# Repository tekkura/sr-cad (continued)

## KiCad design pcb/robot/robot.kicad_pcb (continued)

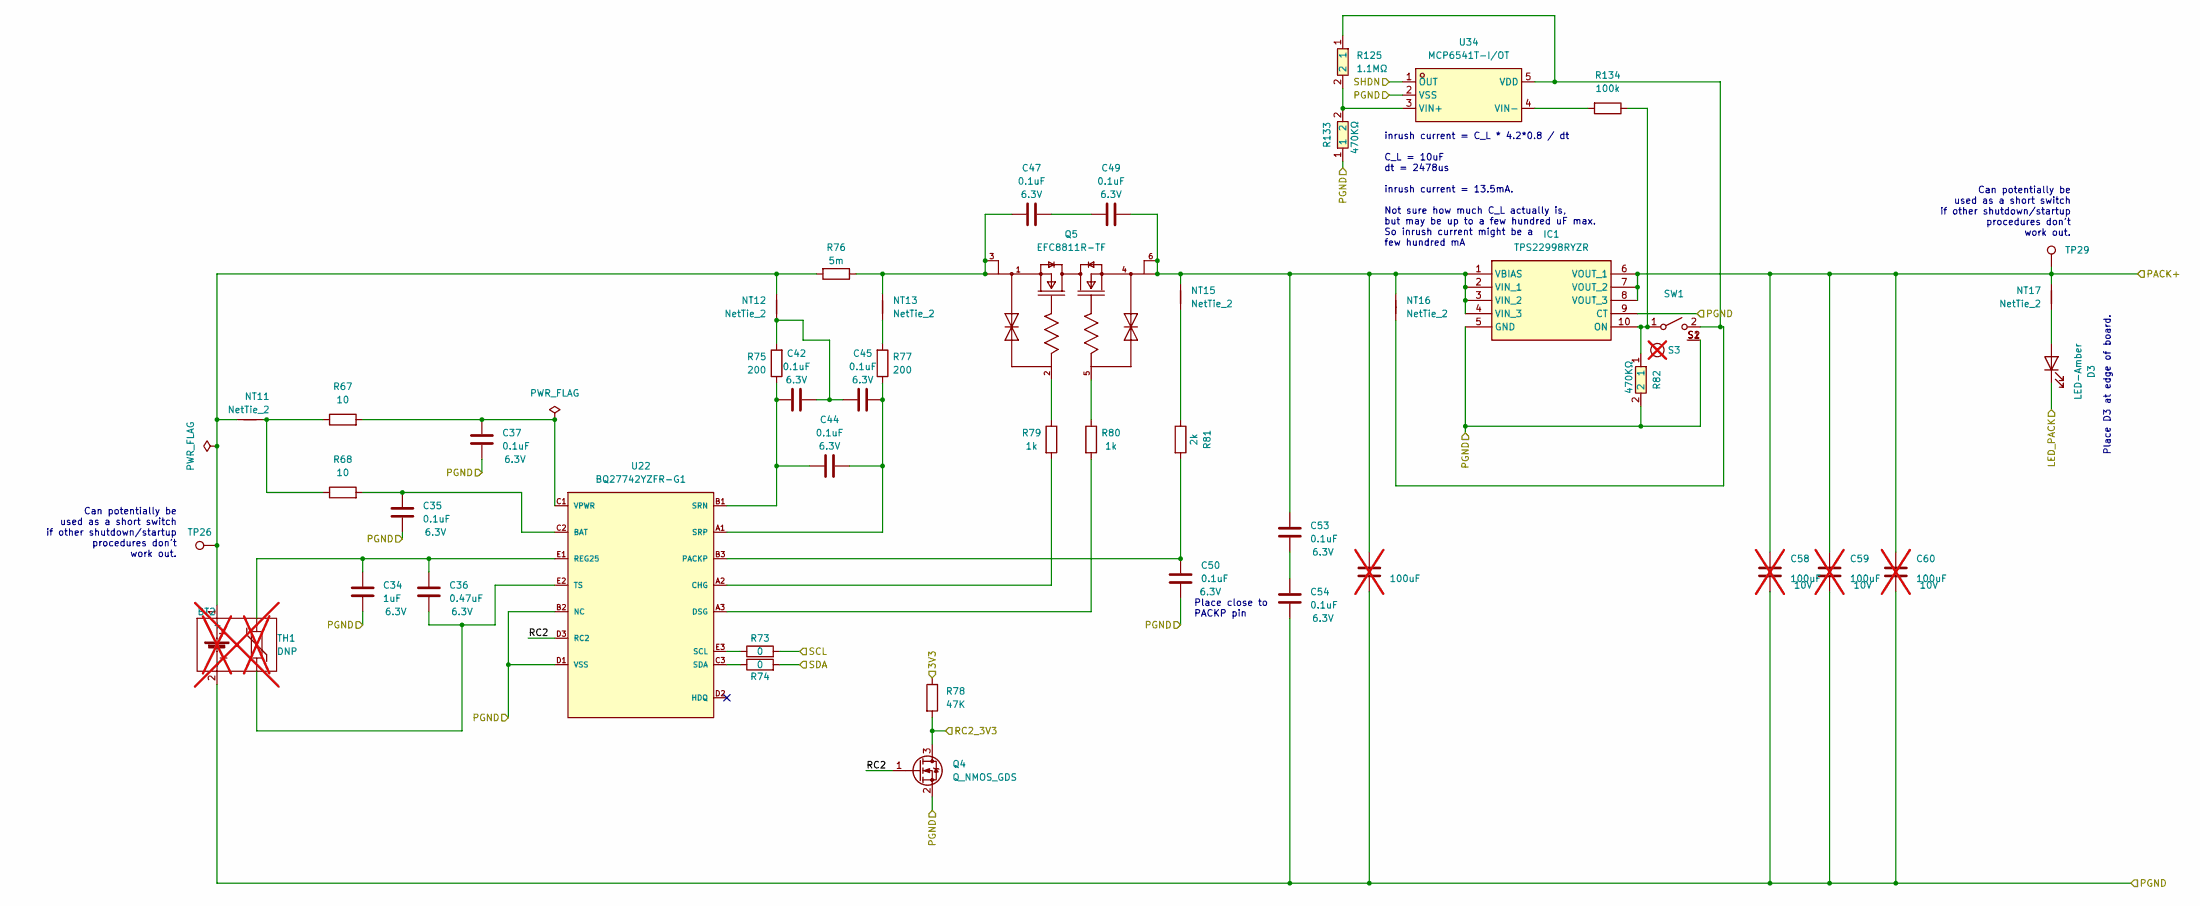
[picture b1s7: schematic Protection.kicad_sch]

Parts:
BT1: DNP; battery26650; Part Number 26650-5000-1; not fitted
BT2: DNP; battery26650_holderOnly; Part Number a15042300ux0145; not fitted
C34: 1uF; C_0402_1005Metric; Part Number GRM155R61E105KA12D
C35, C37, C42, C44, C45, C47, C49, C50, C53, C54: 0.1uF; C_0402_1005Metric; Part Number CL05A104KA5NNNC
C36: 0.47uF; C_0603_1608Metric; Part Number CL10B474KO8NNNC
C56, C58, C59, C60: 100uF; C_1206_3216Metric; Part Number GRM31CD80J107MEA8K; not fitted
D3: LED-Amber; B12H1UYG-20D000134U1930; Part Number B12H1UY--20D000134U1930
IC1: TPS22998RYZR; Part Number TPS22998RYZR
NT11, NT12, NT13, NT15, NT16, NT17: NetTie_2; NetTie-_SMD_Pad6mil; Part Number N/A
Q4: Q_NMOS_GDS; SOT-23; Part Number BSS138
Q5: EFC8811R-TF; ON_Semiconductor-568AL-10_2013-O-MFG; Part Number EFC8811R-TF
R67, R68: 10; R_0402_1005Metric; Part Number RC0402FR-1310RL
R73, R74: 0; R_0603_1608Metric; Part Number RMCF0603ZT0R00
R75, R77: 200; R_0603_1608Metric; Part Number ERJ-PA3J201V
R76: 5m; R_0805_2012Metric; Part Number PA0805FRF470R005L
R78: 47K; R_0603_1608Metric; Part Number RMCF0603JT47K0
R79, R80: 1k; R_0402_1005Metric; Part Number WR04X102 JTL
R81: 2k; R_0603_1608Metric; Part Number RMCF0603FT2K00
R82, R133: 0402WGJ0474TCE; R0402; MPN 0402WGJ0474TCE; LCSC Part C25562
R125: 1.1MΩ; R0402; Part Number 0402WGF1104TCE; LCSC Part C133039
R134: 100k; R_0402_1005Metric; Part Number 0402WGF1003TCE
S3: Part Number SW-R3-1A-A-1-2; not fitted
SW1: SW_SPST; MOLEX_picoblade_SMT_2pin; Part Number 0533980271
TH1: DNP; battery26650_thermistor; Part Number 103AT-5-1P-FT; not fitted
TP26, TP29: TestPoint; THT_JumperLead; Part Number N/A
U22: BQ27742YZFR-G1; Texas_Instruments-YZF0015-0-0-MFG; Part Number BQ27742YZFR-G1
U34: MCP6541T-I/OT; SOT-23-5_L3.0-W1.7-P0.95-LS2.8-BR; Part Number MCP6541T-I/OT; LCSC Part C80839

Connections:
/3V3: R78.1; also elsewhere on the board
/GPIO20: Q4.3 (D), R78.2; also elsewhere on the board
/I2C0_SCL: R73.2; also elsewhere on the board
/I2C0_SDA: R74.2; also elsewhere on the board
/LED_PACK: D3.1 (K); also elsewhere on the board
/Protection/PACK+: C58.1, C59.1, C60.1, IC1.6 (VOUT_1), IC1.7 (VOUT_2), IC1.8 (VOUT_3), NT17.1, TP29.1; also elsewhere on the board
/Protection/RC2: Q4.1 (G), U22.D3 (RC2)
/SHDN: U34.1 (OUT); also elsewhere on the board
GND: BT2.2 (-), C34.2, C35.2, C37.2, C50.2, C54.2, C56.2, C58.2, C59.2, C60.2, IC1.5 (GND), IC1.9 (CT), Q4.2 (S), R82.2, R133.1, SW1.S1, SW1.S2, U22.B2 (NC), U22.D1 (VSS), U34.2 (VSS); also elsewhere on the board
unnamed: BT2.1 (+), NT11.2, NT12.1, R76.2, TP26.1
unnamed: C42.2, C45.1, NT12.2, R75.2
unnamed: C47.1, NT13.1, Q5.1 (SOURCE1), Q5.3 (SOURCE1), R76.1
unnamed: C47.2, C49.1
unnamed: C53.2, C54.1
unnamed: D3.2 (A), NT17.2
unnamed: IC1.10 (ON), R82.1, R134.1, SW1.1 (A)
unnamed: C49.2, C53.1, C56.1, IC1.1 (VBIAS), IC1.2 (VIN_1), IC1.3 (VIN_2), IC1.4 (VIN_3), NT15.1, NT16.1, Q5.4 (SOURCE2), Q5.6 (SOURCE2)
unnamed: NT11.1, R67.1, R68.1
unnamed: NT13.2, R77.2
unnamed: NT15.2, R81.1
unnamed: Q5.2 (GATE1), R79.1
unnamed: Q5.5 (GATE2), R80.1
unnamed: NT16.2, R125.1, SW1.2 (B), U34.5 (VDD)
unnamed: C35.1, R68.2, U22.C2 (BAT)
unnamed: R79.2, U22.A2 (CHG)
unnamed: R80.2, U22.A3 (DSG)
unnamed: C50.1, R81.2, U22.B3 (PACKP)
unnamed: C34.1, C36.1, TH1.1, U22.E1 (REG25)
unnamed: R73.1, U22.E3 (SCL)
unnamed: R74.1, U22.C3 (SDA)
unnamed: C42.1, C44.1, R75.1, U22.B1 (SRN)
unnamed: C44.2, C45.2, R77.1, U22.A1 (SRP)
unnamed: C36.2, TH1.2, U22.E2 (TS)
unnamed: C37.1, R67.2, U22.C1 (VPWR)
unnamed: R125.2, R133.2, U34.3 (VIN+)
unnamed: R134.2, U34.4 (VIN-)

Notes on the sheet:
Can potentially be used as a short switch if other shutdown/startup procedures don't work out.
inrush current = C_L * 4.2*0.8 / dt C_L = 10uF dt = 2478us inrush current = 13.5mA. Not sure how much C_L actually is, but may be up to a few hundred uF max. So inrush current might be a few hundred mA
Place D3 at edge of board.
Place close to PACKP pin

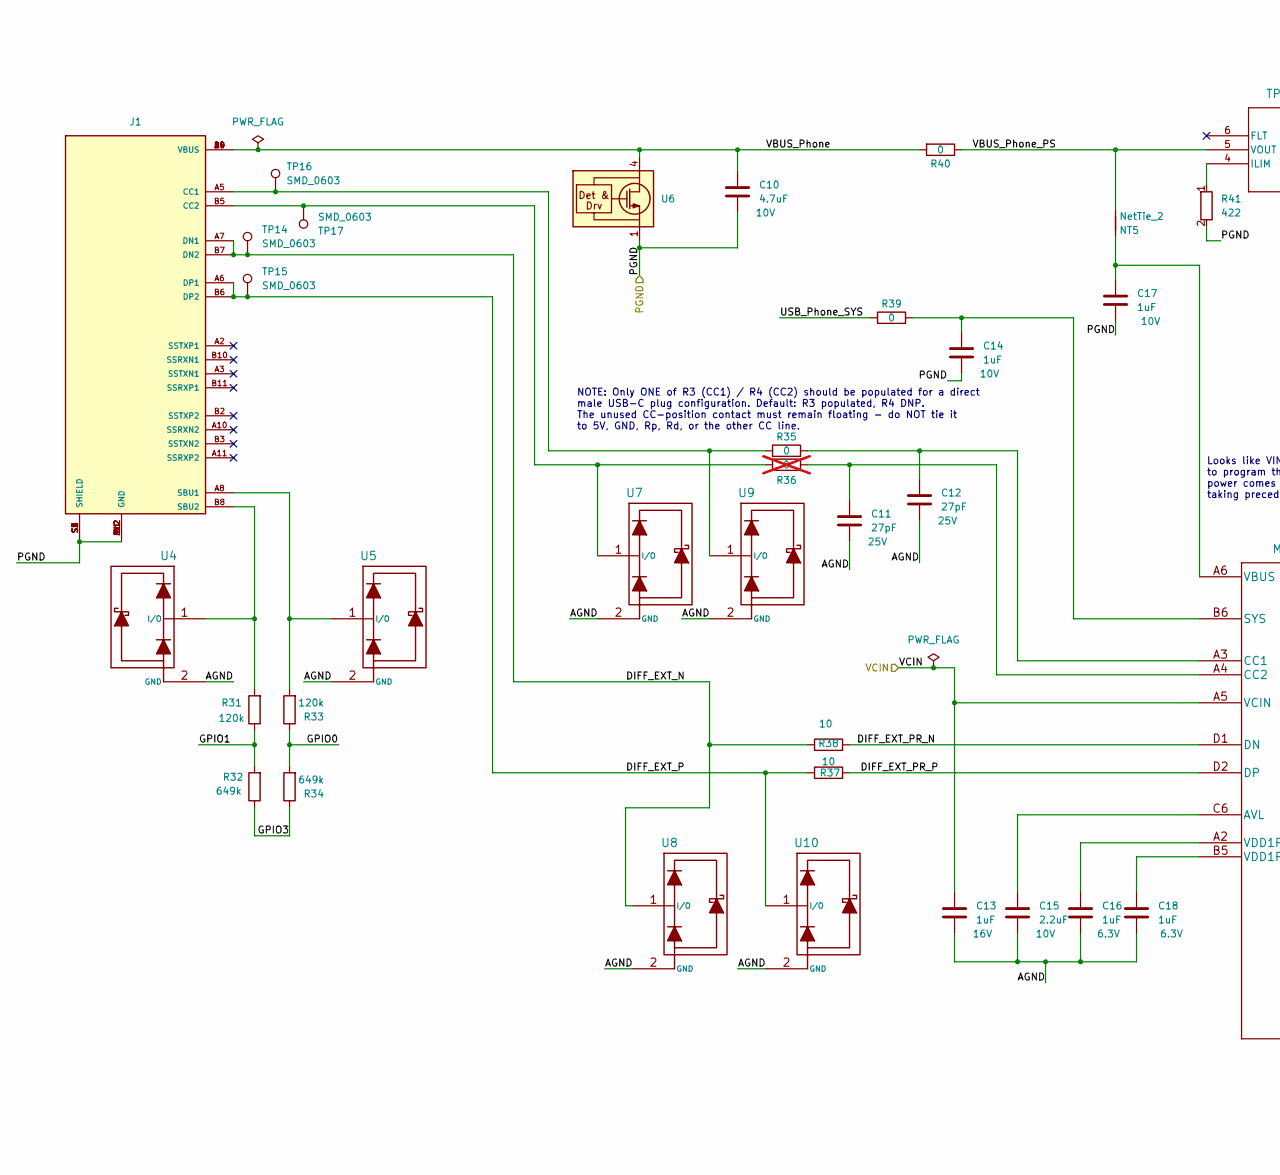
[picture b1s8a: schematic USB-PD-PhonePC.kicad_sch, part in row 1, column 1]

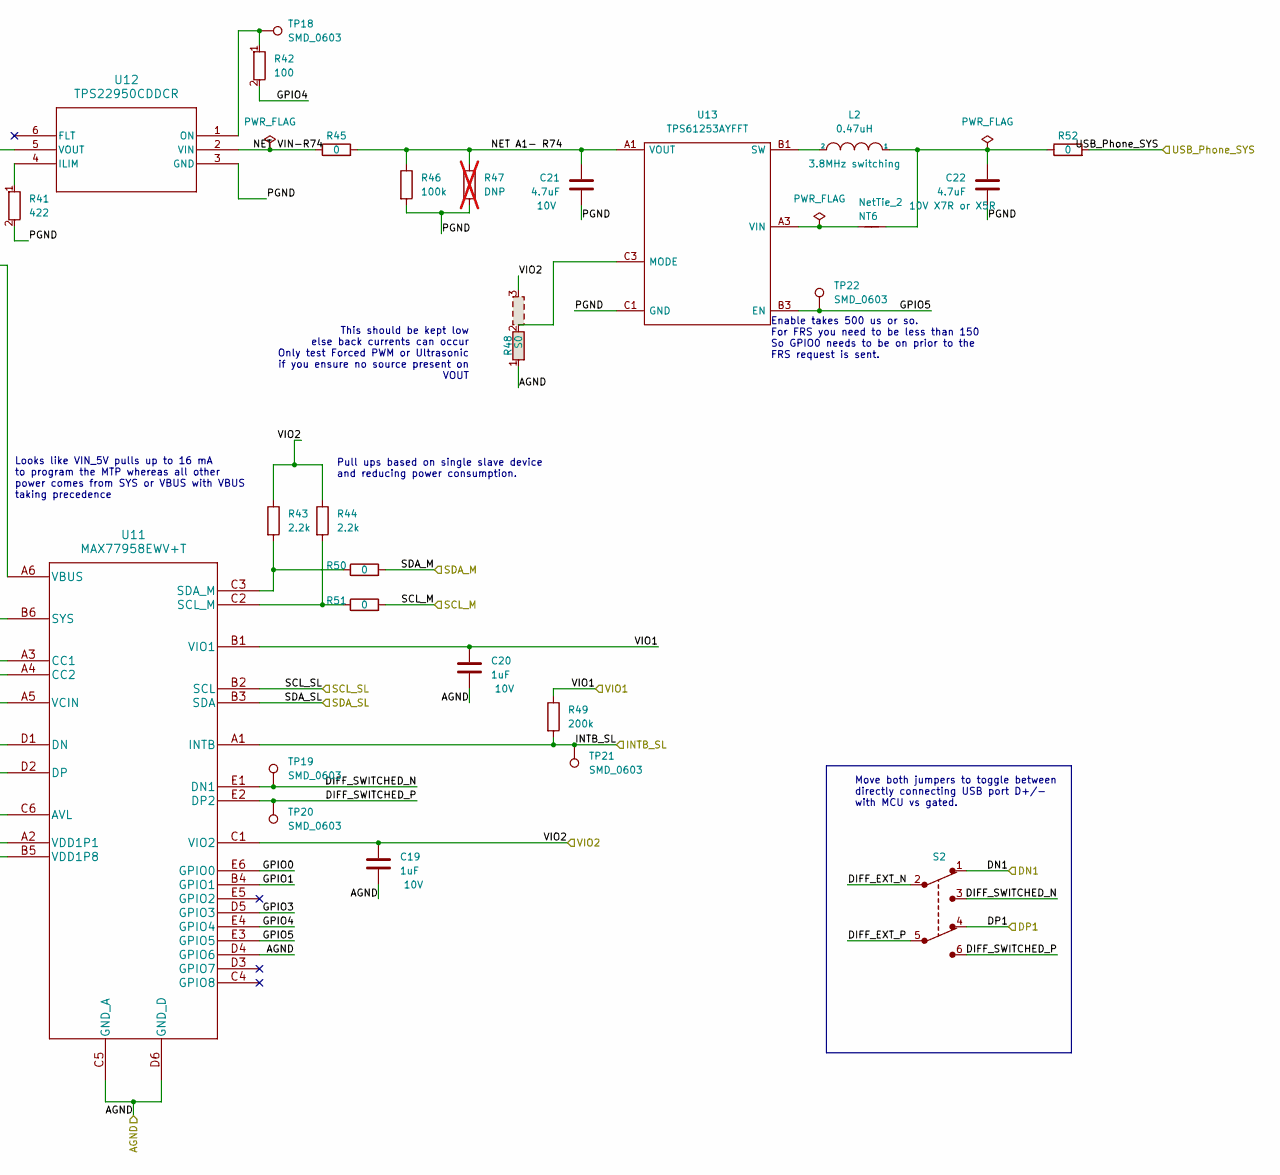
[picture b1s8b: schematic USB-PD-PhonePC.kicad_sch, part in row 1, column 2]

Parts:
C10, C21, C22: 4.7uF; C_0603_1608Metric; Part Number GRM188R61E475KE11D
C11, C12: 27pF; C_0402_1005Metric; Part Number GRM1555C1H270JA01J
C13, C14, C16, C17, C18, C19, C20: 1uF; C_0402_1005Metric; Part Number GRM155R61E105KA12D
C15: 2.2uF; C_0603_1608Metric; Part Number CL10A225KP8NNNC
J1: USB4151-GF-C; GCT_USB4151-GF-C_REVA; Part Number USB4151-GF-C
L2: 0.47uH; Vishay-IHLP-2020BZ-FP_1.905x2.79-3D_2.0-0-0-MFG; Part Number IHLP2020BZERR47M01
NT5, NT6: NetTie_2; NetTie-_SMD_Pad6mil; Part Number N/A
R31, R33: 120k; R_0603_1608Metric; Part Number RMCF0603JT120K
R32, R34: 649k; R_0603_1608Metric; Part Number ERJ-3EKF6493V
R35, R39, R50, R51, R52: 0; R_0603_1608Metric; Part Number RMCF0603ZT0R00
R36: 0; R_0603_1608Metric; Part Number RMCF0603ZT0R00; not fitted
R37, R38: 10; R_0402_1005Metric; Part Number RC0402FR-1310RL
R40, R45: 0; R_0805_2012Metric; Part Number RMCF0805ZT0R00
R41: 422; R_0402_1005Metric; Part Number RC0402FR-07422RL; DigiKey_Part_Number YAG3158CT-ND
R42: 100; R_0402_1005Metric; Part Number RC0402FR-07100RL; DigiKey_Part_Number 311-100LRCT-ND
R43, R44: 2.2k; R_0603_1608Metric; Part Number RMCF0603JT2K20
R46: 100k; R_0603_1608Metric; Part Number WR06X1003FTL
R47: DNP; R_0603_1608Metric; Part Number DNP; not fitted
R48: S0; R_0603_1608Metric_3pin_Switch; Part Number RMCF0603ZT0R00
R49: 200k; R_0603_1608Metric; Part Number RMCF0603JT200K
S2: JS202011JCQN; SW_JS202011JCQN; Part Number JS202011JCQN
TP14, TP15, TP16, TP17, TP18, TP19, TP20, TP21, TP22: SMD_0603; TestPoint_SMD_0603; Part Number RCUCTE
U4, U5, U7, U8, U9, U10: TPD1E05U06; TPD1E05U06DPYR; Part Number TPD1E05U06DPYR
U6: TVS0500DRV; TVS0500DRVR; Part Number TVS0500DRVR
U11: MAX77958EWV+T; MAX77958EWV&plus_T; Part Number MAX77958EWV+T
U12: TPS22950CDDCR; DDC6_TEX; Part Number TPS22950CDDCR
U13: TPS61253AYFFT; Texas_Instruments-YFF0009-BGA9C40P3X3_119X129X62; Part Number TPS61253AYFFT

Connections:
/DN1: S2.1; also elsewhere on the board
/DP1: S2.4; also elsewhere on the board
/GPIO7: R49.2, TP21.1, U11.A1 (INTB); also elsewhere on the board
/I2C1_SCL: R51.2; also elsewhere on the board
/I2C1_SDA: R50.2; also elsewhere on the board
/SCL_SL: U11.B2 (SCL); also elsewhere on the board
/SDA_SL: U11.B3 (SDA); also elsewhere on the board
/USB-PD-PhonePC/DIFF_EXT_N: J1.A7 (DN1), J1.B7 (DN2), R38.1, S2.2, TP14.1, U8.1 (I/O)
/USB-PD-PhonePC/DIFF_EXT_P: J1.A6 (DP1), J1.B6 (DP2), R37.1, S2.5, TP15.1, U10.1 (I/O)
/USB-PD-PhonePC/DIFF_EXT_PR_N: R38.2, U11.D1 (DN)
/USB-PD-PhonePC/DIFF_EXT_PR_P: R37.2, U11.D2 (DP)
/USB-PD-PhonePC/DIFF_SWITCHED_N: S2.3, TP19.1, U11.E1 (DN1)
/USB-PD-PhonePC/DIFF_SWITCHED_P: S2.6, TP20.1, U11.E2 (DP2)
/USB-PD-PhonePC/GPIO0: R33.1, R34.2, U11.E6 (GPIO0)
/USB-PD-PhonePC/GPIO1: R31.1, R32.2, U11.B4 (GPIO1)
/USB-PD-PhonePC/GPIO3: R32.1, R34.1, U11.D5 (GPIO3)
/USB-PD-PhonePC/GPIO4: R42.2, U11.E4 (GPIO4)
/USB-PD-PhonePC/GPIO5: TP22.1, U11.E3 (GPIO5), U13.B3 (EN)
/USB-PD-PhonePC/NET A1- R74: C21.1, R45.2, R46.1, R47.1, U13.A1 (VOUT), U13.A2 (VOUT)
/USB-PD-PhonePC/NET VIN-R74: R45.1, U12.2 (VIN)
/USB-PD-PhonePC/USB_Phone_SYS: R39.1, R52.2; also elsewhere on the board
/USB-PD-PhonePC/VBUS_Phone: C10.1, J1.A4 (VBUS), J1.A9 (VBUS), J1.B4 (VBUS), J1.B9 (VBUS), R40.2, U6.4 (IN), U6.5 (IN), U6.6 (IN)
/USB-PD-PhonePC/VBUS_Phone_PS: NT5.2, R40.1, U12.5 (VOUT)
/USB-PD-PhonePC/VCIN: C13.1, U11.A5 (VCIN); also elsewhere on the board
/USB-PD-PhonePC/VIO1: C20.1, R49.1, U11.B1 (VIO1); also elsewhere on the board
/USB-PD-PhonePC/VIO2: C19.1, R43.1, R44.1, R48.3, U11.C1 (VIO2); also elsewhere on the board
GND: C10.2, C11.2, C12.2, C13.2, C14.2, C15.2, C16.2, C17.2, C18.2, C19.2, C20.2, C21.2, C22.2, J1.A1 (GND), J1.A12 (GND), J1.B1 (GND), J1.B12 (GND), J1.S1 (SHIELD), J1.S2 (SHIELD), J1.S3 (SHIELD), J1.S4 (SHIELD), J1.S5 (SHIELD), R41.2, R46.2, R47.2, R48.1, U4.2 (GND), U5.2 (GND), U6.1 (GND), U6.2 (GND), U6.3 (GND), U6.7 (GND), U7.2 (GND), U8.2 (GND), U9.2 (GND), U10.2 (GND), U11.C5 (GND_A), U11.D4 (GPIO6), U11.D6 (GND_D), U12.3 (GND), U13.C1 (GND), U13.C2 (GND); also elsewhere on the board
unnamed: C22.1, L2.1, NT6.2, R52.1
unnamed: J1.A5 (CC1), R35.1, TP16.1, U9.1 (I/O)
unnamed: J1.B5 (CC2), R36.1, TP17.1, U7.1 (I/O)
unnamed: J1.A8 (SBU1), R33.2, U5.1 (I/O)
unnamed: J1.B8 (SBU2), R31.2, U4.1 (I/O)
unnamed: L2.2, U13.B1 (SW), U13.B2 (SW)
unnamed: C15.1, U11.C6 (AVL)
unnamed: C12.1, R35.2, U11.A3 (CC1)
unnamed: C11.1, R36.2, U11.A4 (CC2)
unnamed: R44.2, R51.1, U11.C2 (SCL_M)
unnamed: R43.2, R50.1, U11.C3 (SDA_M)
unnamed: C14.1, R39.2, U11.B6 (SYS)
unnamed: C17.1, NT5.1, U11.A6 (VBUS)
unnamed: C16.1, U11.A2 (VDD1P1)
unnamed: C18.1, U11.B5 (VDD1P8)
unnamed: R41.1, U12.4 (ILIM)
unnamed: R42.1, TP18.1, U12.1 (ON)
unnamed: R48.2, U13.C3 (MODE)
unnamed: NT6.1, U13.A3 (VIN)

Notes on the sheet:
Pull ups based on single slave device and reducing power consumption.
Looks like VIN_5V pulls up to 16 mA to program the MTP whereas all other power comes from SYS or VBUS with VBUS taking precedence
This should be kept low else back currents can occur Only test Forced PWM or Ultrasonic if you ensure no source present on VOUT
Move both jumpers to toggle between directly connecting USB port D+/- with MCU vs gated.
NOTE: Only ONE of R3 (CC1) / R4 (CC2) should be populated for a direct male USB-C plug configuration. Default: R3 populated, R4 DNP. The unused CC-position contact must remain floating - do NOT tie it to 5V, GND, Rp, Rd, or the other CC line.
Enable takes 500 us or so. For FRS you need to be less than 150 So GPIO0 needs to be on prior to the FRS request is sent.

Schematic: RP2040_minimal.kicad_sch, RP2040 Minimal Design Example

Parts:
C66, C67: 27pF; C_0402_1005Metric; Part Number GRM1555C1H270JA01J
C74, C89, C96, C111, C115, C117, C120, C123, C124, C125, C127, C128: 0.1uF; C_0402_1005Metric; Part Number CL05A104KA5NNNC
C97, C112: 1uF; C_0402_1005Metric; Part Number GRM155R61E105KA12D
C126: 10uF; C_0603_1608Metric; Part Number GRM188R61E106KA73J
C129, C130: 0.1uF; C_0402_1005Metric; Part Number CL05A104KA5NNNC; not fitted
J9: Conn_01x05; PinSocket_1x05_P2.54mm_Vertical; Part Number PH1-05-UA
R88, R104: 1k; R_0402_1005Metric; Part Number WR04X102 JTL
R92: DNP; R_0402_1005Metric; Part Number DNP; not fitted
R107: 0; R_0603_1608Metric; Part Number RMCF0603ZT0R00; not fitted
R114, R115: 27; R_0402_1005Metric; Part Number RMCF0402JT27R0
R116: 422k; R_0603_1608Metric; Part Number RT0603BRD07422KL
R117: 100k; R_0603_1608Metric; Part Number WR06X1003FTL
R118, R120: 100; R_0603_1608Metric; Part Number RMCF0603JT100R; not fitted
R119, R121: 100k; R_0402_1005Metric; Part Number 0402WGF1003TCE
S4: PTS815 SJM 250 SMTR LFS; SW4_PTS815 SJM 250 SMTR LFS_CNK; Part Number PTS815 SJM 250 SMTR LFS
TP31, TP32, TP33, TP34, TP35, TP36: SMD_0603; TestPoint_SMD_0603; Part Number RCUCTE
U24: W25Q128JVS; SOIC-8_5.23x5.23mm_P1.27mm; Part Number W25Q128JVSIQ
U29: RP2040; RP2040-QFN-56; Part Number SC0914(13)
U30, U31: TPS3808G01DBVR; SOT-23-6_L2.9-W1.6-P0.95-LS2.8-BR; Part Number TPS3808G01DBVR; LCSC Part C19653
Y1: ECS-120-8-36-CKM-TR3; XTAL_ECS-120-8-36-CKM-TR3; Part Number ECS-120-8-36-CKM-TR3

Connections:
/GPIO4: U29.6 (GPIO4); also elsewhere on the board
/GPIO5: U29.7 (GPIO5); also elsewhere on the board
/GPIO6: U29.8 (GPIO6); also elsewhere on the board
/GPIO7: U29.9 (GPIO7); also elsewhere on the board
/GPIO8: U29.11 (GPIO8); also elsewhere on the board
/GPIO9: U29.12 (GPIO9); also elsewhere on the board
/GPIO10: U29.13 (GPIO10); also elsewhere on the board
/GPIO11: U29.14 (GPIO11); also elsewhere on the board
/GPIO12: U29.15 (GPIO12); also elsewhere on the board
/GPIO13: U29.16 (GPIO13); also elsewhere on the board
/GPIO14: U29.17 (GPIO14); also elsewhere on the board
/GPIO15: U29.18 (GPIO15); also elsewhere on the board
/GPIO20: U29.31 (GPIO20); also elsewhere on the board
/GPIO22: U29.34 (GPIO22); also elsewhere on the board
/GPIO23: U29.35 (GPIO23); also elsewhere on the board
/I2C0_SCL: U29.3 (GPIO1); also elsewhere on the board
/I2C0_SDA: U29.2 (GPIO0); also elsewhere on the board
/I2C1_SCL: U29.5 (GPIO3); also elsewhere on the board
/I2C1_SDA: U29.4 (GPIO2); also elsewhere on the board
/LED_EN: U29.32 (GPIO21); also elsewhere on the board
/MCU/3V3: C74.1, C111.1, C112.1, C115.1, C117.1, C120.1, C123.1, C124.1, C125.1, C126.1, C127.1, C128.1, R92.1, R119.1, R121.1, U24.8 (VCC), U29.1 (IOVDD), U29.10 (IOVDD), U29.22 (IOVDD), U29.33 (IOVDD), U29.42 (IOVDD), U29.43 (ADC_AVDD), U29.44 (VREG_IN), U29.48 (USB_VDD), U29.49 (IOVDD), U30.3 (MR), U30.6 (VDD), U31.3 (MR), U31.6 (VDD); also elsewhere on the board
/MCU/ADC2: R120.2, TP33.1
/MCU/ADC3: R118.2, TP34.1
/MCU/D+: R114.1; also elsewhere on the board
/MCU/D-: R115.1; also elsewhere on the board
/MCU/GPIO24: TP35.1, U29.36 (GPIO24)
/MCU/GPIO25: TP36.1, U29.37 (GPIO25)
/MCU/GPIO26_USB_INT: R119.2, U29.38 (GPIO26_ADC0), U30.1 (RESET)
/MCU/GPIO27_WLC_INT: R121.2, U29.39 (GPIO27_ADC1), U31.1 (RESET)
/MCU/GPIO28_ADC2: C130.1, R120.1, U29.40 (GPIO28_ADC2)
/MCU/GPIO29_ADC3: C129.1, R118.1, U29.41 (GPIO29_ADC3)
/MCU/QSPI_SCLK: U24.6 (CLK), U29.52 (QSPI_SCLK)
/MCU/QSPI_SD0: U24.5 (DI(IO0)), U29.53 (QSPI_SD0)
/MCU/QSPI_SD1: U24.2 (DO(IO1)), U29.55 (QSPI_SD1)
/MCU/QSPI_SD2: U24.3 (IO2), U29.54 (QSPI_SD2)
/MCU/QSPI_SD3: U24.7 (IO3), U29.51 (QSPI_SD3)
/MCU/QSPI_SS: R88.1, R92.2, U24.1 (~CS), U29.56 (QSPI_SS)
/MCU/RUN: R107.2, U29.26 (RUN)
/MCU/SWCLK: J9.2, U29.24 (SWCLK)
/MCU/SWD: J9.3, U29.25 (SWD)
/MCU/UART_CTS: TP31.1, U29.29 (GPIO18)
/MCU/UART_RTS: TP32.1, U29.30 (GPIO19)
/MCU/UART_RX: J9.5, U29.28 (GPIO17)
/MCU/UART_TX: J9.4, U29.27 (GPIO16)
/MCU/XIN: C66.1, U29.20 (XIN), Y1.1
/MCU/XOUT: R104.1, U29.21 (XOUT)
/MCU/~USB_BOOT: R88.2, S4.1, S4.2
/USB_SNS: U30.5 (SENSE); also elsewhere on the board
/VRect: R116.1; also elsewhere on the board
GND: C66.2, C67.2, C74.2, C89.2, C96.2, C97.2, C111.2, C112.2, C115.2, C117.2, C120.2, C123.2, C124.2, C125.2, C126.2, C127.2, C128.2, C129.2, C130.2, J9.1, R107.1, R117.2, S4.3, S4.4, U24.4 (GND), U29.19 (TESTEN), U29.57 (GND), U30.2 (GND), U31.2 (GND), Y1.2 (GND), Y1.4 (GND); also elsewhere on the board
unnamed: C67.1, R104.2, Y1.3
unnamed: R115.2, U29.46 (USB_DM)
unnamed: R114.2, U29.47 (USB_DP)
unnamed: C89.1, C96.1, C97.1, U29.23 (DVDD), U29.45 (VREG_VOUT), U29.50 (DVDD)
unnamed: R116.2, R117.1, U31.5 (SENSE)

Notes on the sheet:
Make sure C8 is close to pin 45 of RP2040
TPS3808 voltage supervisors replace the passive divider+RC filter (fixes #19) - GPIO26_USB_INT/GPIO27_WLC_INT are now digital interrupt inputs, not ADC channels. Firmware: use GPIO input + edge interrupt, do not sample via ADC. U30/U31 = TPS3808G01DBVR (adjustable, SOT-23-6, LCSC C19653). SENSE vs 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
Make sure C10 is close to pin 44 of RP2040
Flash
Crystal
Make sure R3 and R4 are close to RP2040

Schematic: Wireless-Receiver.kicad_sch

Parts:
C62, C78, C81: 22nF; C_0402_1005Metric; Part Number GRM155R71H223KA12J
C63: 1.5nF; C_0402_1005Metric; Part Number GCM155R71H152KA37D
C64, C85: 3.3nF; C_0402_1005Metric; Part Number GCM155R71H332KA37J
C69, C92, C94: 100uF; C_1206_3216Metric; Part Number GRM31CD80J107MEA8K
C70, C72, C76, C80, C84: 0.1uF; C_0402_1005Metric; Part Number GRM155R62A104KE14D
C73, C79: 10nF; C_0402_1005Metric; Part Number 885012205067
C88, C95: 47nF; C_0402_1005Metric; Part Number GRM155R71H473KE14D
C91: 4.7uF; C_0603_1608Metric; Part Number GRM188R61E475KE11D
C93: 1uF; C_0402_1005Metric; Part Number GRM155R61E105KA12D
C98, C99, C104, C109, C114: 10uF; C_0603_1608Metric; Part Number GRM188R61E106KA73J
C103: 100uF; C_1210_3225Metric; Part Number GRM31CD80J107MEA8K
C106, C110, C121: 100uF; C_1210_3225Metric; Part Number GMC32X5R107M16NT; not fitted
C118: 100uF; C_1210_3225Metric; Part Number GMC32X5R107M16NT
D4, D5: IN4448HLP; D_0402_1005Metric; Part Number 1N4448HLP-7
D8, D9, D10: SMF13A; D_SOD-123F; Part Number SMF13A
J4: Conn_01x02; THT_Pitch5mm_Drill1.2mm; Part Number N/A
L4: 8uH; Part Number 760308102207; not fitted
R83, R89: 10k; R_0603_1608Metric; Part Number WR06X1002FTL
R84: 150k; R_0402_1005Metric; Part Number RC0402FR-13150KL
R85, R110: 100k; R_0603_1608Metric; Part Number WR06X1003FTL
R86: 220k; R_0402_1005Metric; Part Number RC0402FR-07220KL
R87: 6.8k; R_0402_1005Metric; Part Number RC0402FR-136K8L
R108, R109: 0; R_0603_1608Metric; Part Number RMCF0603ZT0R00
R111, R112: 200; R_0603_1608Metric; Part Number ERJ-PA3J201V
R113: 200; R_0603_1608Metric; Part Number ERJ-PA3J201V; not fitted
TH2: 100k; R_0402_1005Metric; Part Number NCU15WF104J6SRC
U27: STWLC38JRM; BGA40C40P5X8_213X333X57; Part Number STWLC38JRM

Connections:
/GPIO9: U27.G4 (ENB); also elsewhere on the board
/GPIO23: R110.2, U27.H4 (INTB); also elsewhere on the board
/I2C0_SCL: R109.2; also elsewhere on the board
/I2C0_SDA: R108.2; also elsewhere on the board
/PowerMux/VIN_B: C98.2, C99.2, C103.2, C106.2, C110.2, U27.E1 (VOUT_1), U27.E2 (VOUT_2); also elsewhere on the board
/VRect: C104.2, C109.2, C114.2, C118.2, C121.2, D10.1 (K), R111.2, R112.2, R113.2, U27.D1 (VRECT_1), U27.D2 (VRECT_2), U27.D3 (VRECT_3), U27.D4 (VRECT_4), U27.D5 (VRECT_5); also elsewhere on the board
/Wireless-Receiver/IEXT: R111.1, R112.1, R113.1, U27.A3 (IEXT)
/Wireless-Receiver/VAA: C91.2, C92.2, R84.2, R89.1, R110.1, U27.E4 (VAA)
/Wireless-Receiver/VDD: C93.2, C94.2, U27.F4 (VDD)
GND: C63.1, C64.1, C69.2, C91.1, C92.1, C93.1, C94.1, C98.1, C99.1, C103.1, C104.1, C106.1, C109.1, C110.1, C114.1, C118.1, C121.1, D4.2 (A), D8.2 (A), D9.2 (A), D10.2 (A), R85.1, R86.2, TH2.2, U27.A1 (VSSP_1), U27.A2 (VSSP_2), U27.A4 (VSSP_3), U27.A5 (VSSP_4), U27.E5 (VSSA), U27.F5 (VSSD); also elsewhere on the board
unnamed: C62.2, R83.2
unnamed: C64.2, R83.1, R86.1, R87.2
unnamed: C62.1, C63.2, D4.1 (K), R84.1, R85.2, U27.F2 (VS)
unnamed: C70.1, C72.1, C76.1, C80.1, C84.1, D5.2 (A), J4.2, L4.1
unnamed: D5.1 (K), R87.1
unnamed: C70.2, C72.2, C73.2, C76.2, C78.2, C80.2, C84.2, C85.1, C95.2, D8.1 (K), U27.B4 (AC1_1), U27.B5 (AC1_2), U27.C4 (AC1_3), U27.C5 (AC1_4)
unnamed: C79.2, C81.2, C85.2, C88.2, D9.1 (K), J4.1, L4.2, U27.B1 (AC2_1), U27.B2 (AC2_2), U27.C1 (AC2_3), U27.C2 (AC2_4)
unnamed: C95.1, U27.B3 (BOOT1)
unnamed: C88.1, U27.C3 (BOOT2)
unnamed: C73.1, U27.G1 (COMA1)
unnamed: C79.1, U27.G2 (COMA2)
unnamed: C78.1, U27.H1 (COMB1)
unnamed: C81.1, U27.H2 (COMB2)
unnamed: C69.1, R89.2, TH2.1, U27.F1 (NTC)
unnamed: R109.1, U27.H5 (SCL)
unnamed: R108.1, U27.G5 (SDA)

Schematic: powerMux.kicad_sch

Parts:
C23, C24: 1uF; C_0402_1005Metric; Part Number GRM155R61E105KA12D
C25: 4.7uF; C_0603_1608Metric; Part Number GRM188R61E475KE11D
Q1: Q_NMOS_GDS; SOT-23; Part Number BSS138
R53: 1M; R_0603_1608Metric; Part Number FRC0603F1004TS
R54: 100k; R_0603_1608Metric; Part Number WR06X1003FTL
R55: 47K; R_0603_1608Metric; Part Number RMCF0603JT47K0
U14: NCP3901; Part Number NCP3901FCCT1G

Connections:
/GPIO4: Q1.3 (D), R55.2; also elsewhere on the board
/GPIO5: U14.D2 (VINA_EN/OTG_EN); also elsewhere on the board
/PowerMux/FLAG: Q1.1 (G), U14.D3 (VINB_EN/FLAG)
/PowerMux/VIN_A: C23.1, U14.A1 (VINA), U14.A2 (VINA), U14.A3 (VINA), U14.A4 (VINA), U14.A5 (VINA), U14.A6 (VINA), U14.A7 (VINA); also elsewhere on the board
/PowerMux/VIN_B: C24.1, U14.D4 (VINB), U14.D5 (VINB), U14.D6 (VINB), U14.D7 (VINB); also elsewhere on the board
/PowerMux/VIO: R55.1; also elsewhere on the board
/PowerMux/VOUT: C25.1, U14.B5 (OUT), U14.B6 (OUT), U14.B7 (OUT), U14.C4 (OUT), U14.C5 (OUT), U14.C6 (OUT), U14.C7 (OUT); also elsewhere on the board
/USB_SNS: R53.2, R54.1; also elsewhere on the board
GND: C23.2, C24.2, C25.2, Q1.2 (S), R54.2, U14.B1 (GND), U14.B2 (GND), U14.B3 (GND), U14.C1 (MODE), U14.C2 (GND), U14.C3 (GND), U14.D1 (CRTL); also elsewhere on the board
unnamed: R53.1, U14.B4 (VINA_S)

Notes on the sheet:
Internal 500K PD
VINA_S used to report to MCU current limited analog voltage.
Internal 100K PU
Internal 50K PU
Can range from 0V - V_USB_BUS_MAX (5V?). Although with USB-PD this could go up to 20V, The USB-PD chip should limit this to 5V as there is no reason to have higher voltages for a wired charger on a single 4.2V LiPo Cell. Divider to scale down to 3.3V.
Priority given to VIN_A so place USB-C on VIN_A and wireless on VIN_B
Turn on/off USB-OTG. OTG on when pin HIGH. High between 1.2 and 5.5V
FLAG used to report to MCU valid boolean voltage. Should be 1.8V.
Set MODE and CTRL to Low to enable unlocked autonomous mode

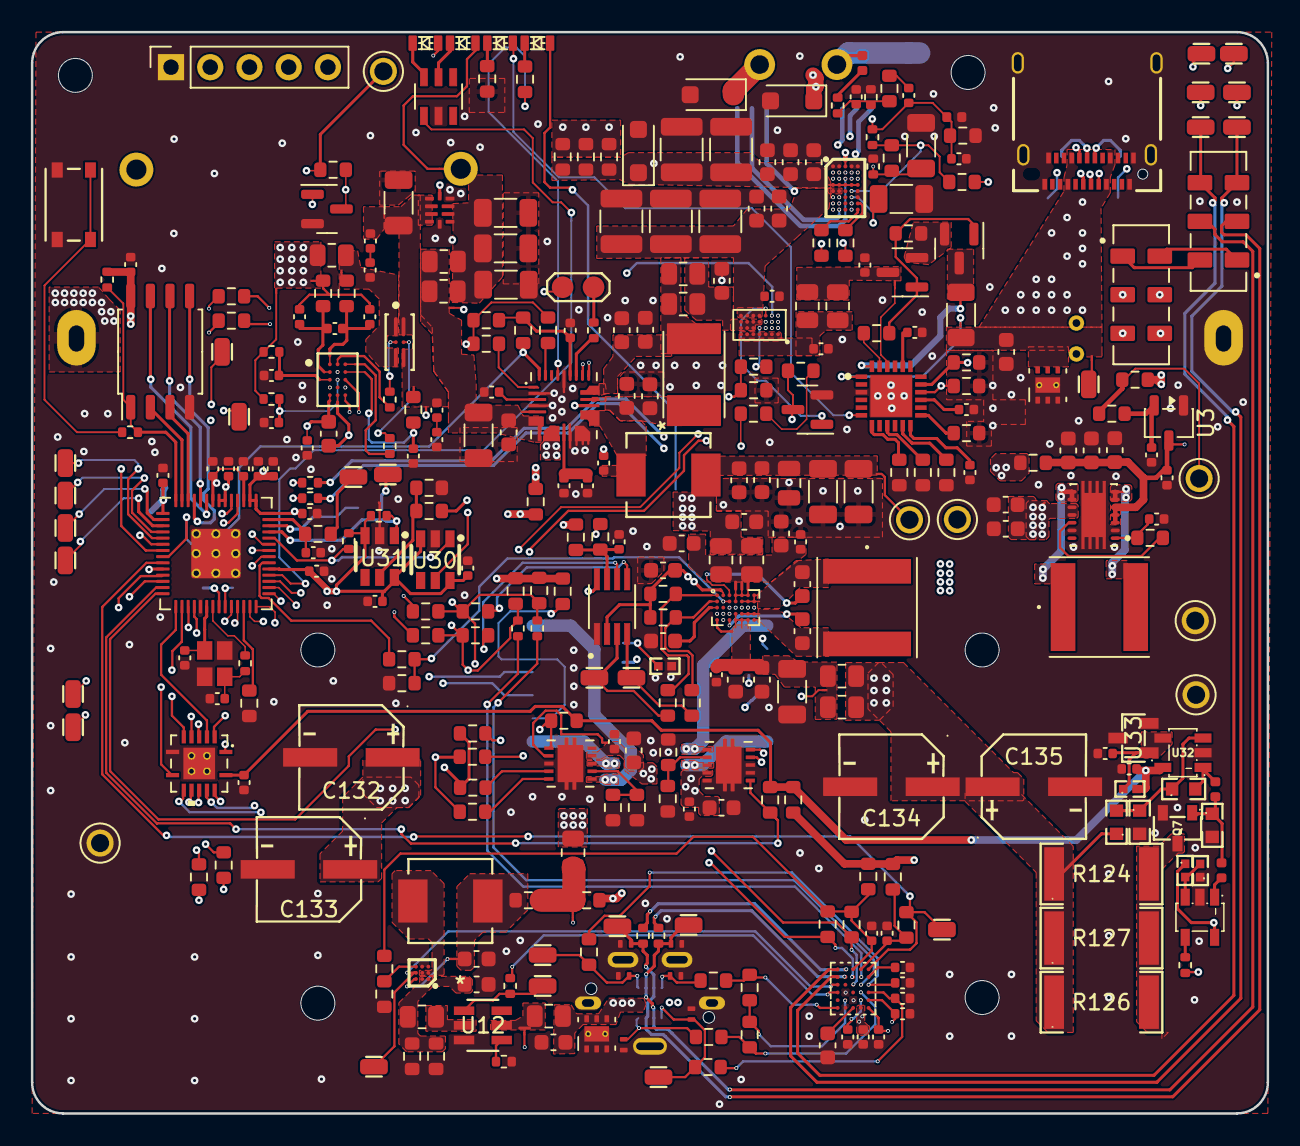
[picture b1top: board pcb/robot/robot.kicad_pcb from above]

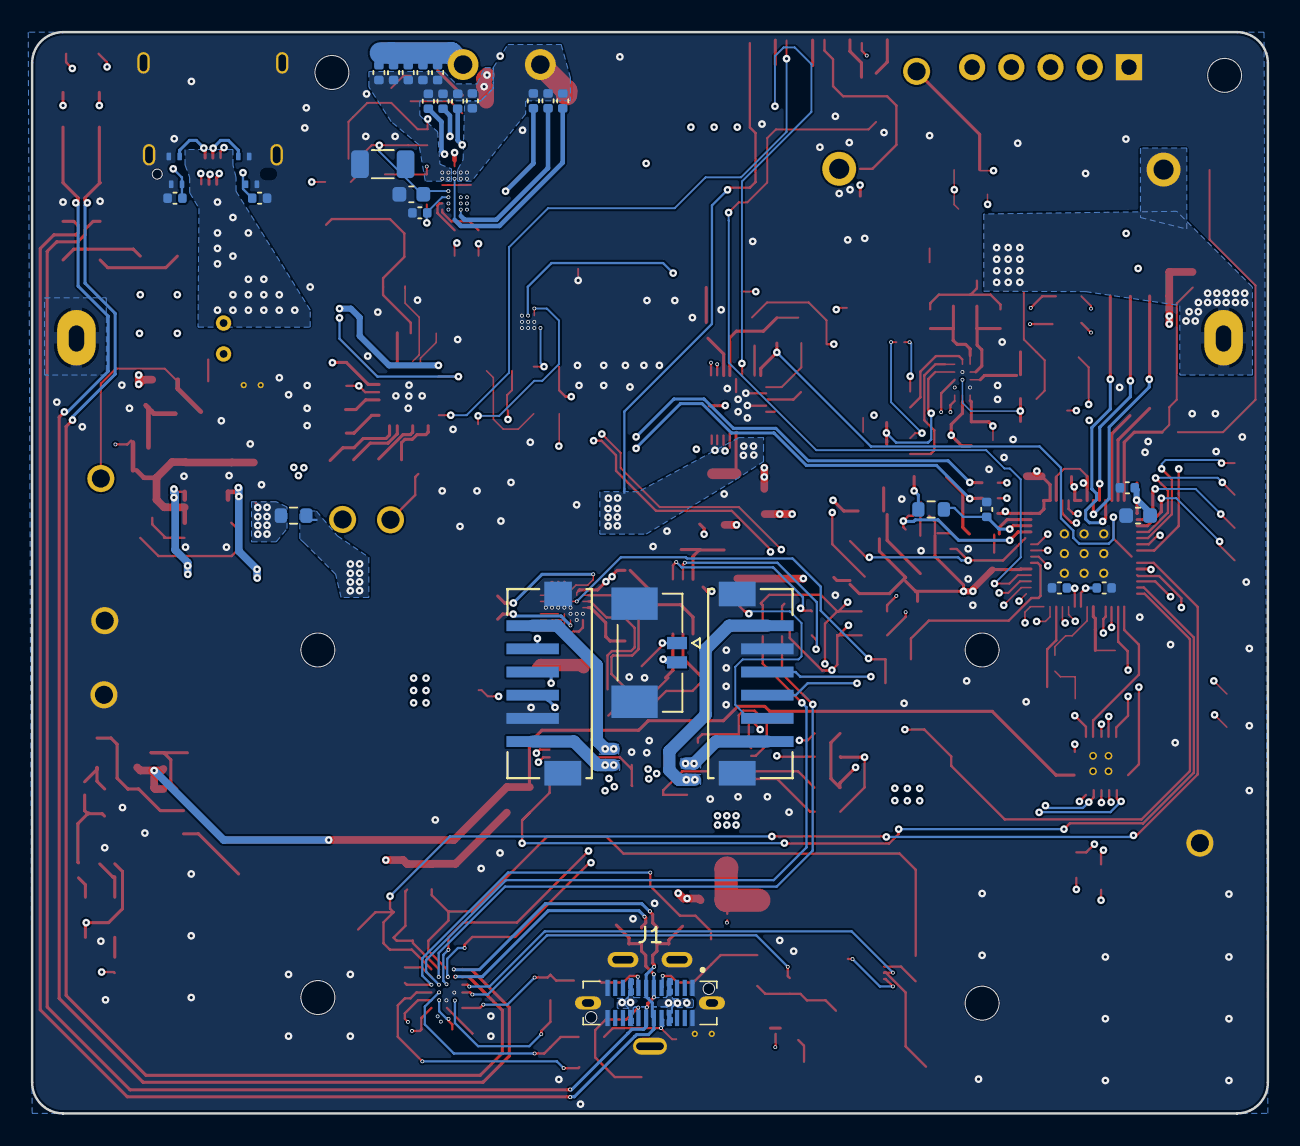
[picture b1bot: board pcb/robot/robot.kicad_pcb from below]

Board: 4 copper layers, 80.0 x 70.0 mm, 408 parts (37 on the bottom side), 250 nets.
